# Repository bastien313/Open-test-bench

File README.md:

[Ce README en français](README_fr.md)
# Open test bench

## Introduction

Open test bench is an open-source platform for drive or characterize any type of system.
The system is made for simplifying the development of additional modules called "peripheral module".
User connect his computer to backplane unit which gives an access to the peripheral.

#### Composition
- Backplane unit.
- Some peripheral module.
- Module d'extension (TBD).

## Description

### Backplane unit

Backplane unit is the main block of the system.
It can receive 4 peripherals modules and link user computer to peripheral module.
More peripherals modules can be added with the extension module but with slower communication speed.

#### Backplane unit implement
- A microcontroller STM32H7.
- Some channel communication to peripheral modules(SPI 50Mhz, UART 10Mhz, I2C 1Mhz, GPIO).
- A driver UART <-> USB (FT230H) 12Mb/s.
- A driver TBD <-> USB ou ETHERNET for high speed communication.
- Connectors for plug peripheral module.
- Possibility to add extension module for low-speed peripheral modules.

### Peripheral module

Peripheral modules make links with the real world.
Each module has an access to 4 communication channels dedicated.
- SPI with CS
- UART with RTS/CTS
- I2C
- 8 GPIO

Peripheral have an acces to another I2C (I2C_CONTROL) for implement a litle memory (EEPROM) used for calibration data.

#### Peripheral split
2 connectors is used for a peripheral module, it can be split in two peripherial:
- Top module have acces to SPI and UART.
- Bottom module have acces to 8 GPIO and I2C.
Each module have an acces to I2C_CONTROL for implement their own EEPROM.

#### Wide capability
- Voltage/current measurement.
- Sensor measurement.
- Digital input/output.
- Power management.
- ....

#### Suggested format of peripheral module
- Galvanic isolation for simplifying referenced problems.
- EEPROM for saves needed calibration.
- Mechanical dimension (TBD), capability of a double module.

### Extension module
Extension module can extend the capabilties of the backplane with lower speed.
Each communication channel(UART, I2C, SPI) is multiplexed to each peripheral module.
GPIO expander is used for manage the 8 bottom GPIO.

### Preliminary definition

### Extension definition

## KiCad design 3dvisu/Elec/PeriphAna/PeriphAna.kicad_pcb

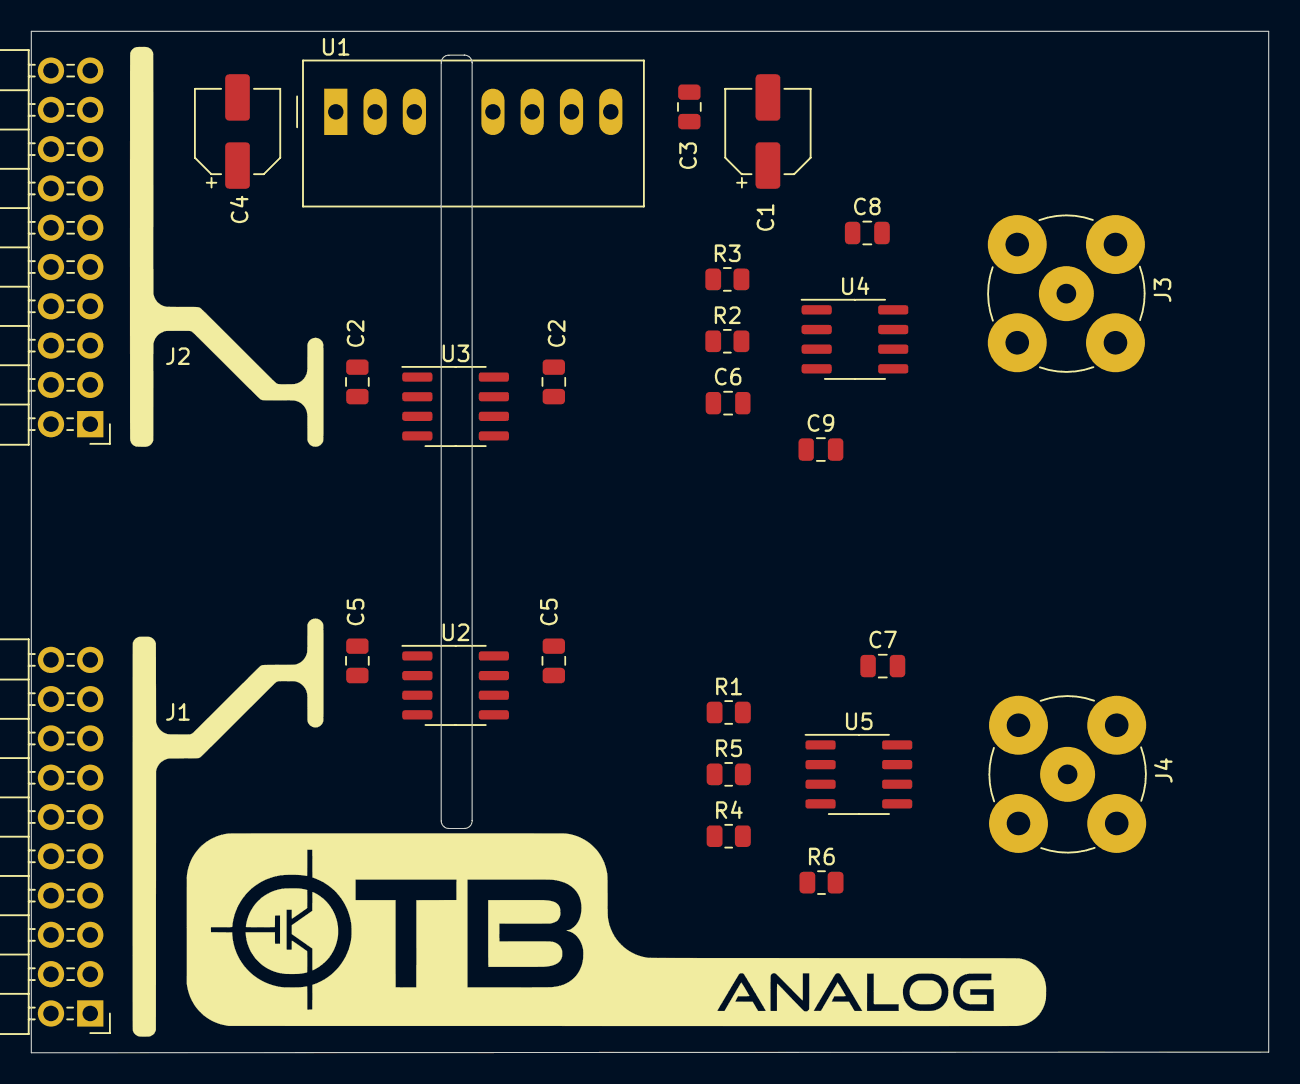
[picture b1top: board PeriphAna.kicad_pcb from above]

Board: 2 copper layers, 80.0 x 66.0 mm, 26 parts (0 on the bottom side), 4 nets, no tracks yet.

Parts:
C1, C4: CP1; CP_Elec_5x5.7
C2, C2#2, C3, C5, C5#2, C6, C7, C8, C9: C; C_0805_2012Metric
J1, J2: Conn_02x10_Counter_Clockwise; PinHeader_2x10_P2.54mm_Horizontal
J3, J4: Conn_Coaxial; BNC_TEConnectivity_1478204_Vertical
R1, R2, R3, R4, R5, R6: R; R_0805_2012Metric
U1: TMR-2412; Converter_DCDC_TRACO_TMR-xxxx_THT
U2, U3: ADuM1200WT; SOIC-8_3.9x4.9mm_P1.27mm
U4, U5: OPA2333xxD; SOIC-8_3.9x4.9mm_P1.27mm

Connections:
unnamed: C2.1, C2#2.1
unnamed: C2.2, C2#2.2
unnamed: C5.1, C5#2.1
unnamed: C5.2, C5#2.2

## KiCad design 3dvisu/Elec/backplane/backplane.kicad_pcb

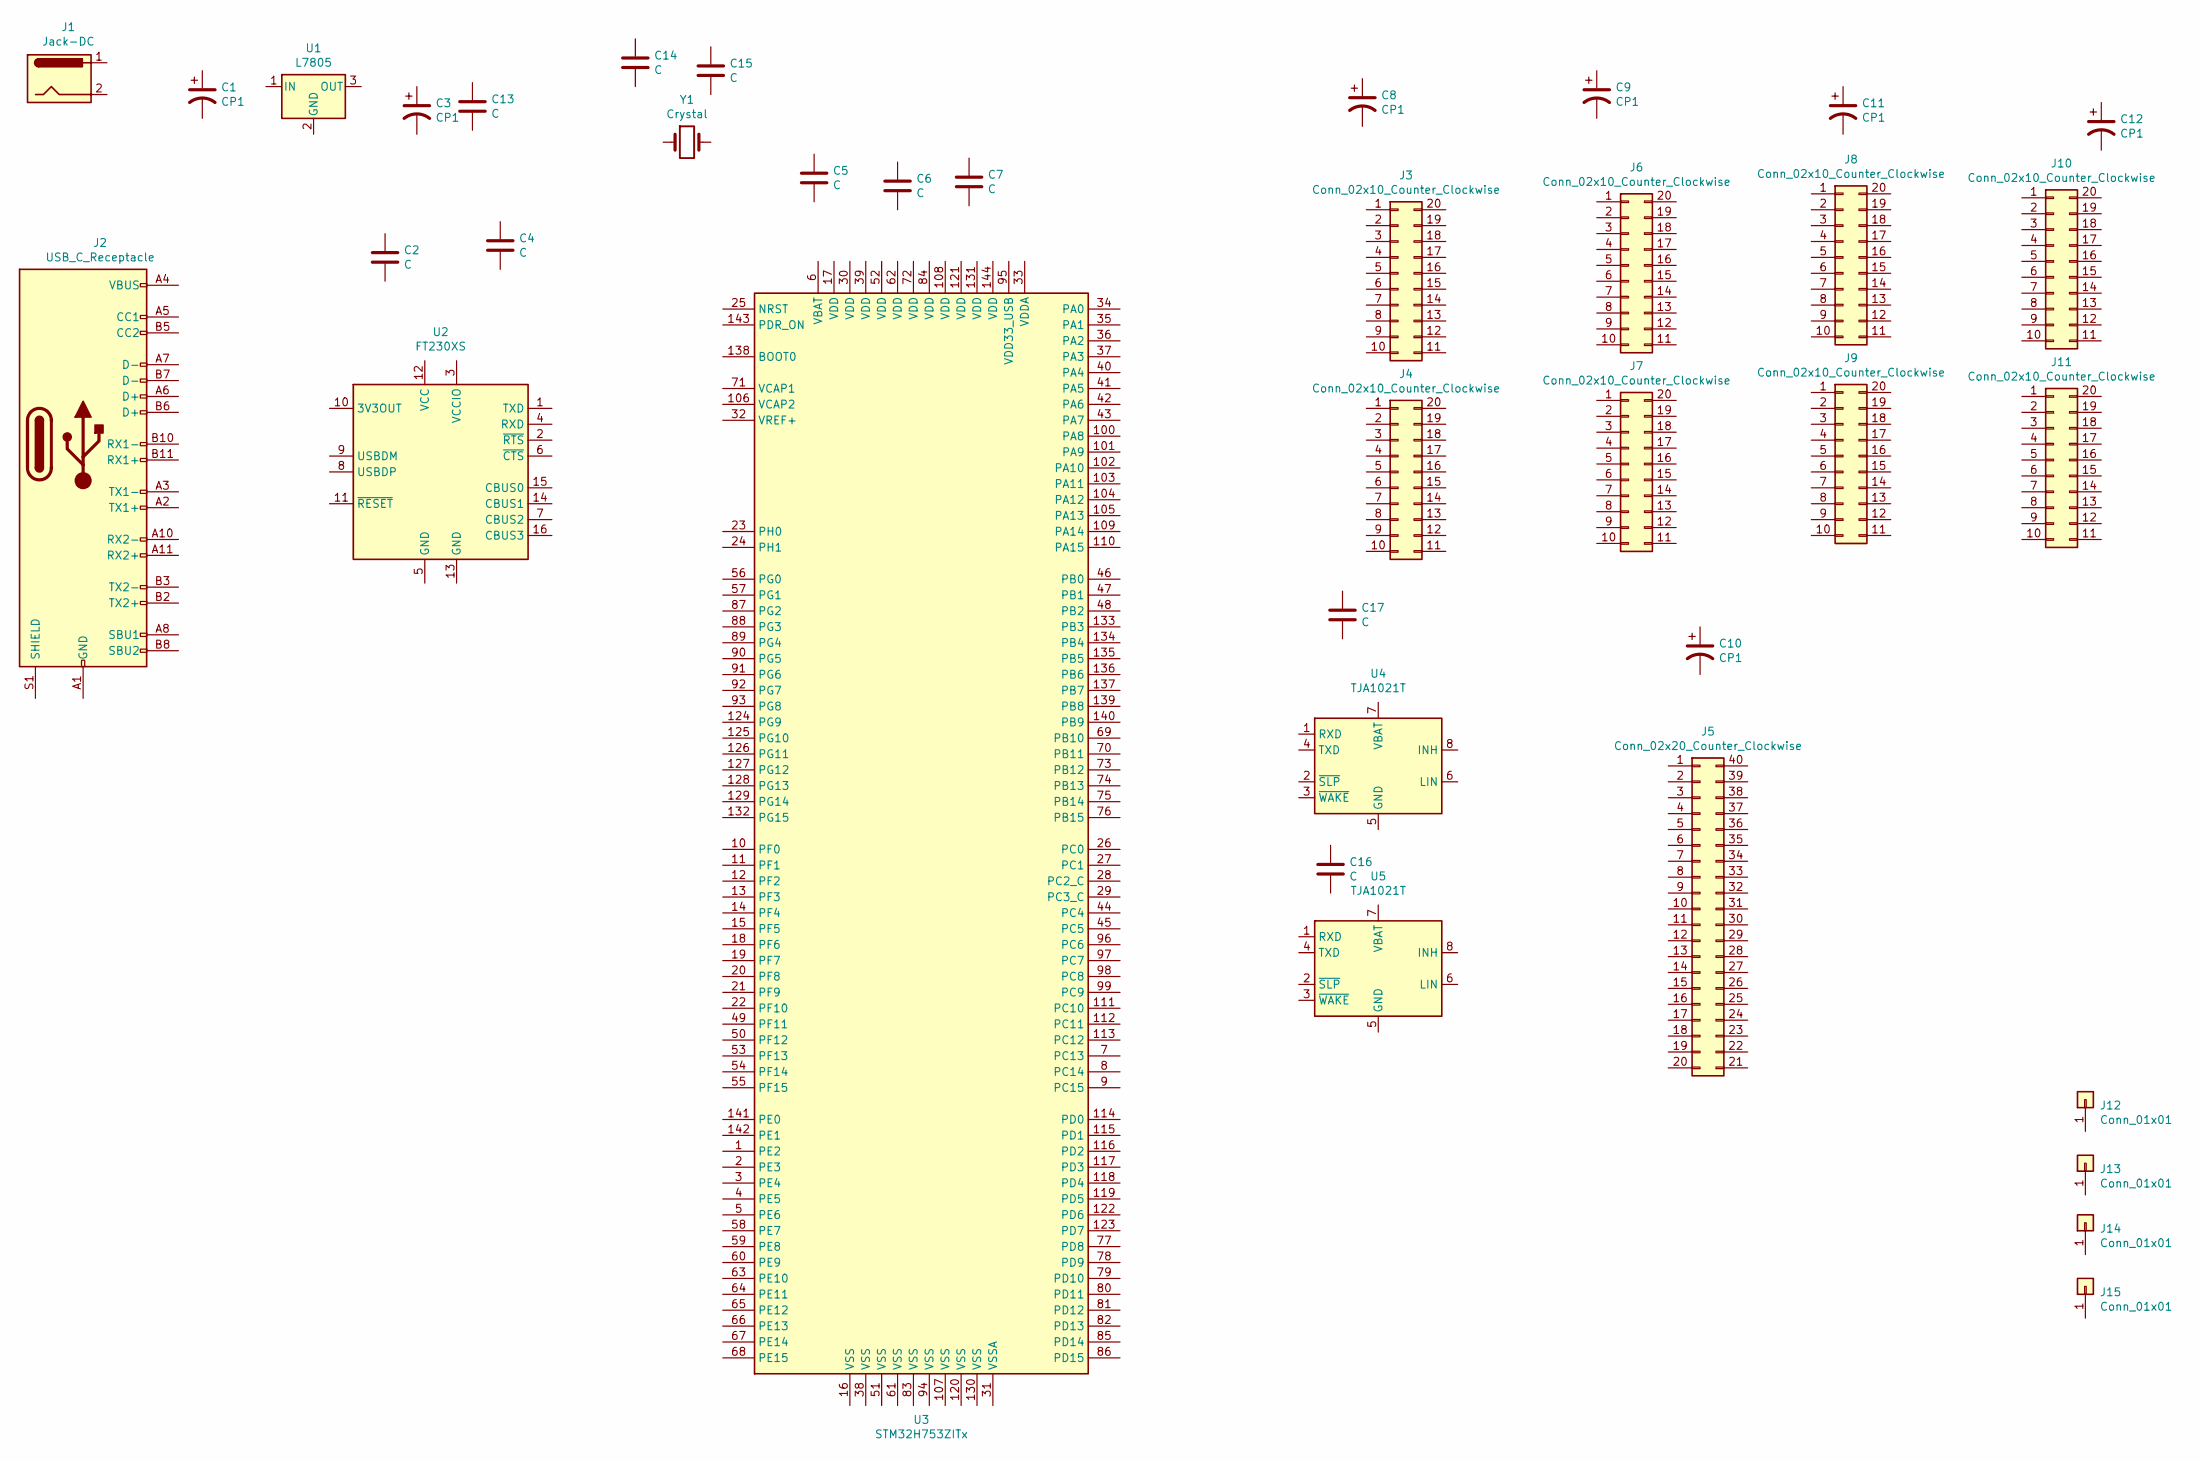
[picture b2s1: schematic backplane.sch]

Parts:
C1, C3, C8, C9, C10, C11, C12: CP1; CP_Elec_6.3x3
C2, C4, C5, C6, C7, C13, C14, C15, C16, C17: C; C_0805_2012Metric
J1: Jack-DC; BarrelJack_CUI_PJ-102AH_Horizontal
J2: USB_C_Receptacle; USB_C_Receptacle_Amphenol_12401548E4-2A
J3, J4, J6, J7, J8, J9, J10, J11: Conn_02x10_Counter_Clockwise; PinSocket_2x10_P2.54mm_Vertical_SMD
J5: Conn_02x20_Counter_Clockwise; PinSocket_2x20_P2.54mm_Horizontal
J12, J13, J14, J15: Conn_01x01; MountingHole_3.2mm_M3_Pad_Via
U1: L7805; TO-252-2_TabPin1
U2: FT230XS; SSOP-16_3.9x4.9mm_P0.635mm
U3: STM32H753ZITx; LQFP-144_20x20mm_P0.5mm
U4, U5: TJA1021T; SOIC-8_3.9x4.9mm_P1.27mm
Y1: Crystal; Crystal_SMD_3225-4Pin_3.2x2.5mm

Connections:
unnamed: J2.A1 (GND), J2.A12 (GND), J2.B1 (GND), J2.B12 (GND)
unnamed: J2.A4 (VBUS), J2.A9 (VBUS), J2.B4 (VBUS), J2.B9 (VBUS)

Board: 2 copper layers, 38 parts (25 on the bottom side), 2 nets, no tracks yet.

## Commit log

2021-04-30 Create LICENSE
2021-04-30 Start prelim def
2021-05-01 Maj definition
2021-05-02 backplane on going
2021-05-06 render made
2021-05-16 assignation connecteur
2021-05-24 Choixe uC + start assign
2021-05-24 choice uC + assign
2021-05-26 stm32h7 symbol made
2021-05-26 stm32h7 symbol made+lib
2021-05-27 assign uC OK
2021-06-01 Switch stm32h725 to stm32h723
2021-06-01 Update def
2021-06-01 Extend definition
2021-06-01 Extend definition2
2021-06-01 ethernet start
2021-06-01 eth on goign
2021-08-31 ajout ft232h
2021-09-20 schematic presque ok
